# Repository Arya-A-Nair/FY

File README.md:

# FY

Important Links:

<hr>
<ul>
    <li>
        <a href="https://drive.google.com/drive/folders/1RNFaYqhC2TZiy3xr0IBFxQ6YlD5DJD_7?usp=sharing">Past year
        </a>
    </li>
</ul>

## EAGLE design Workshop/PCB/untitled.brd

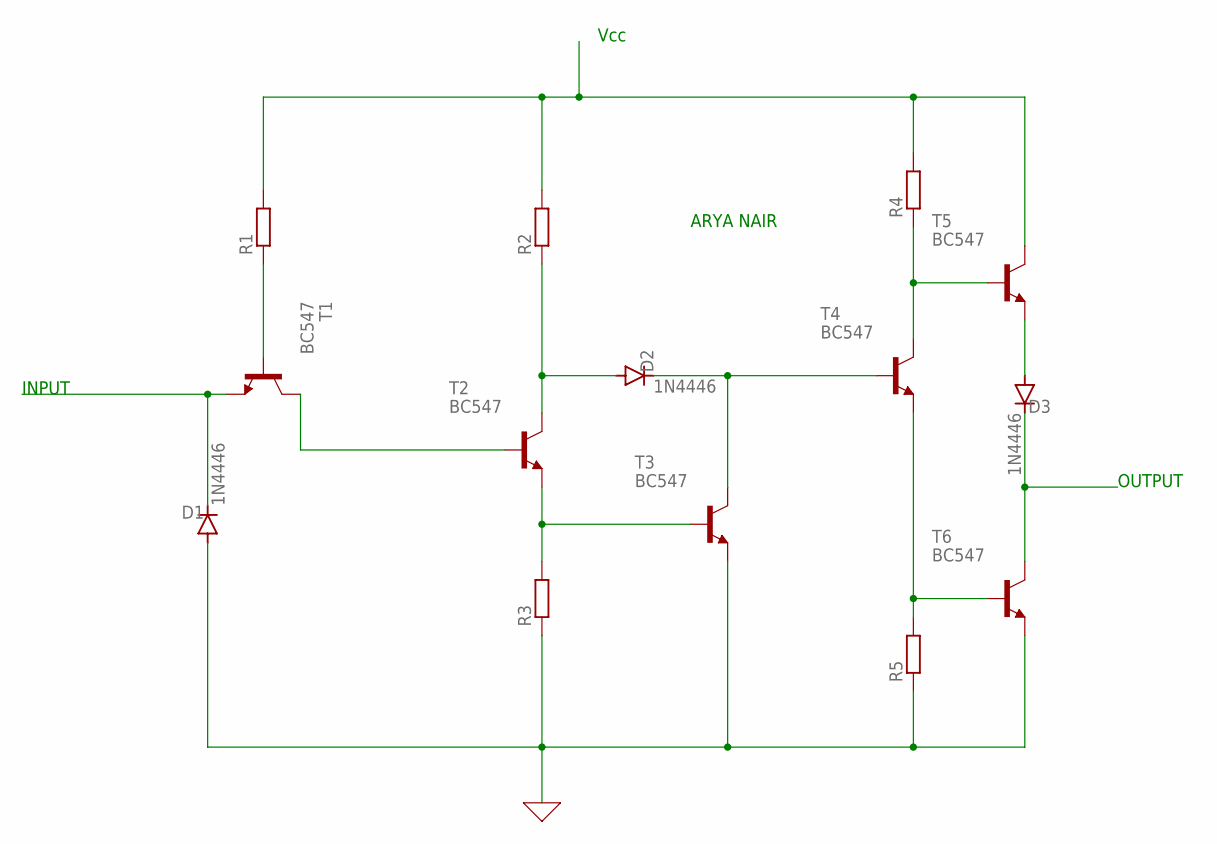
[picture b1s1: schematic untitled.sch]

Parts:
D1, D2, D3: 1N4446; DO35-10
R1, R2, R3, R4, R5: R-EU_0204/2V; 0204V
T1, T2, T3, T4, T5, T6: BC547; TO92

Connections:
0: D1.A, R3.1, R5.1, T3.1 (E), T6.1 (E)
unnamed: T1.3 (C), T2.2 (B)
unnamed: R3.2, T2.1 (E), T3.2 (B)
unnamed: D2.A, R2.1, T2.3 (C)
unnamed: R1.2, R2.2, R4.2, T5.3 (C)
unnamed: R1.1, T1.2 (B)
unnamed: D1.C, T1.1 (E)
unnamed: D2.C, T3.3 (C), T4.2 (B)
unnamed: R4.1, T4.3 (C), T5.2 (B)
unnamed: D3.A, T5.1 (E)
unnamed: R5.2, T4.1 (E), T6.2 (B)
unnamed: D3.C, T6.3 (C)

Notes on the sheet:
Vcc
OUTPUT
INPUT
ARYA NAIR

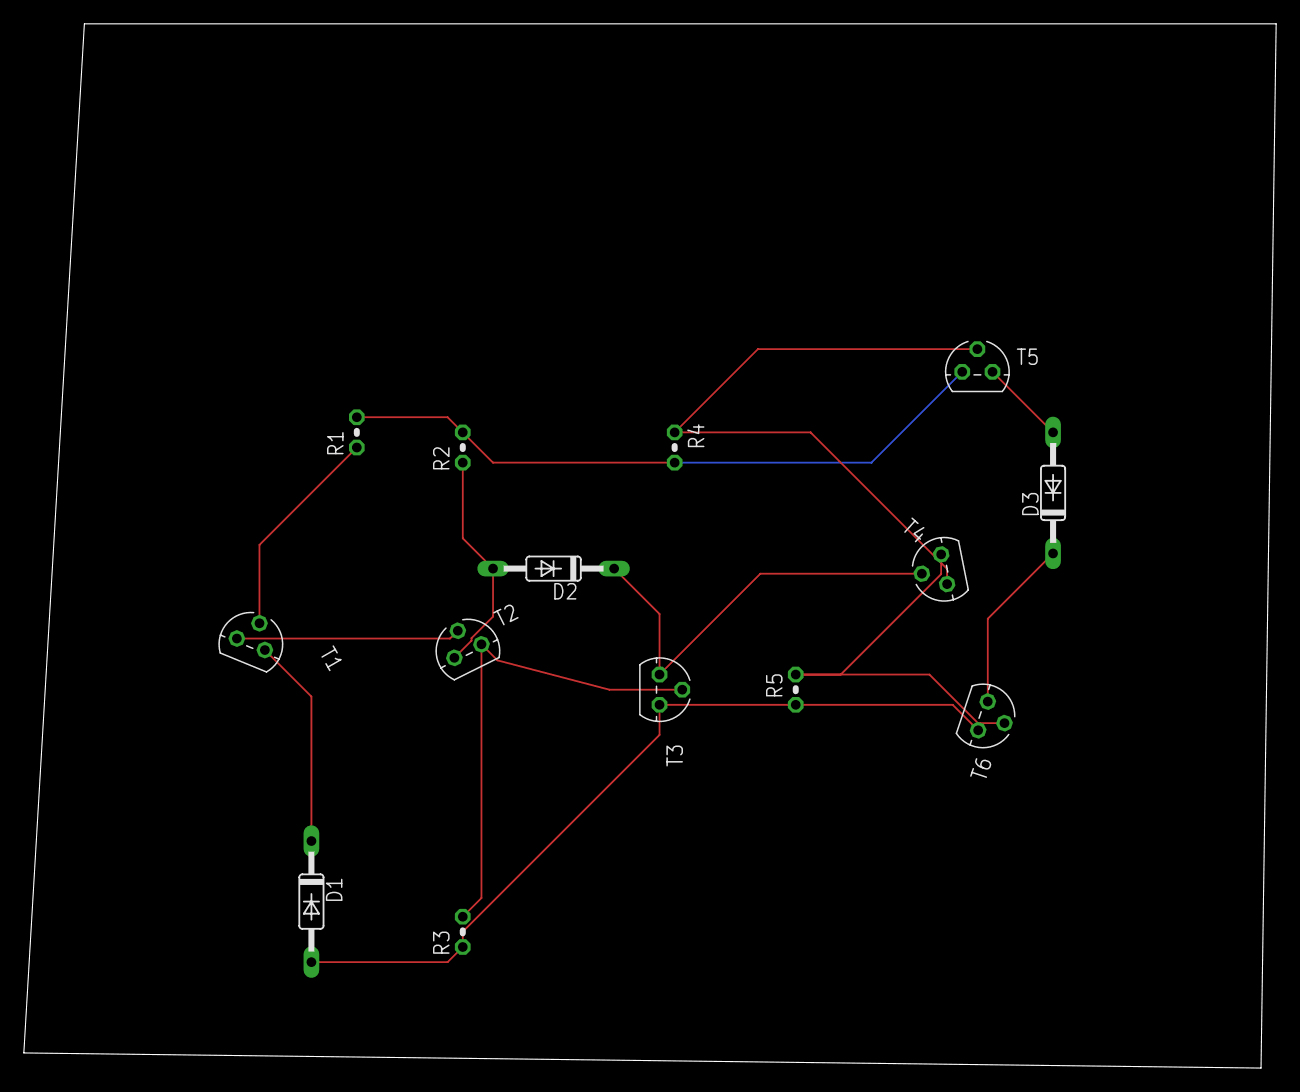
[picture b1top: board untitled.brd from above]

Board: 2 copper layers, 105.1 x 87.6 mm, 14 parts (0 on the bottom side), 12 nets.

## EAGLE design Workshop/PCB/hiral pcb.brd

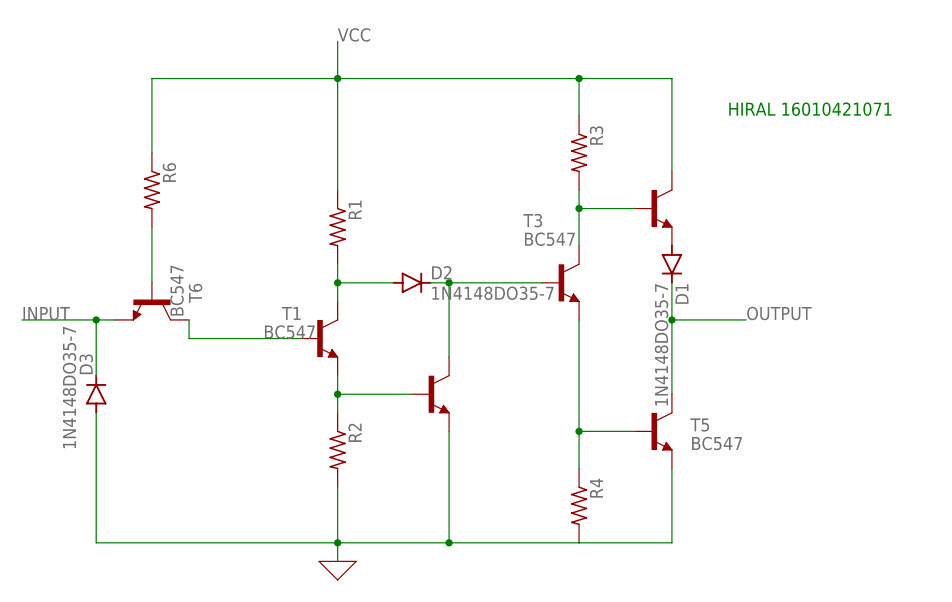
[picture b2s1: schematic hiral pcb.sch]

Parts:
D1, D2, D3: 1N4148DO35-7; DO35-7
R1, R2, R3, R4, R6: R-US_0204/5; 0204/5
T1, T2, T3, T4, T5, T6: BC547; TO92

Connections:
0: D3.A, R2.2, R4.2, T2.1 (E), T5.1 (E)
INPUT: D3.C, T6.1 (E)
unnamed: R6.2, T6.2 (B)
unnamed: D1.A, T4.1 (E)
unnamed: R4.1, T3.1 (E), T5.2 (B)
unnamed: D2.A, R1.2, T1.3 (C)
unnamed: R2.1, T1.1 (E), T2.2 (B)
unnamed: R3.2, T3.3 (C), T4.2 (B)
unnamed: D2.C, T2.3 (C), T3.2 (B)
unnamed: T1.2 (B), T6.3 (C)
OUTPUT: D1.C, T5.3 (C)
VCC: R1.1, R3.1, R6.1, T4.3 (C)

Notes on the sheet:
HIRAL 16010421071

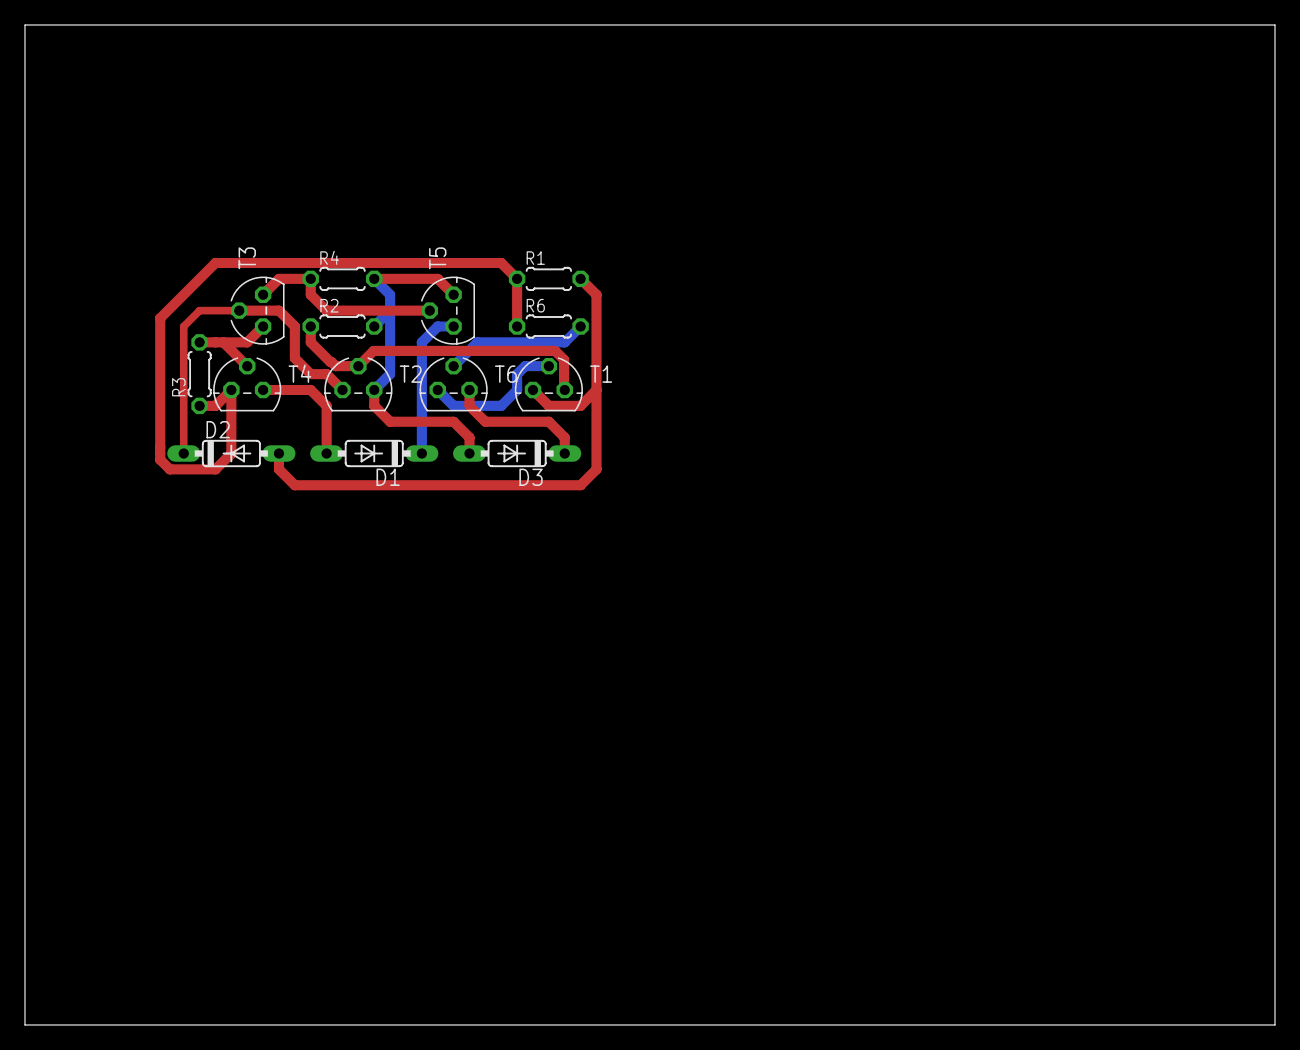
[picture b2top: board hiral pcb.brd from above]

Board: 2 copper layers, 100.0 x 80.0 mm, 14 parts (0 on the bottom side), 12 nets.

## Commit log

2022-08-01 AM-I
2022-08-01 AM-II
2022-08-01 EEEE
2022-08-01 EP theory
2022-08-01 workshop
2023-12-27 Python IA practice added.
